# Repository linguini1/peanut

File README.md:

# Peanut 

A modern, tiny, and hackable altimeter for hobby rocketry.

[Peanut is certified as open-source hardware by the Open Source Hardware
Association (CA000081).][oshw-cert]

<p align="center">
    
    <br/>
    Peanut Altimeter with my fingers for scale
</p>

<p align="center">
    
    <br/>
    Peanut Altimeter powered up and operational
</p>

<p align="center">
    
    <br/>
    Peanut Altimeter KiCAD render
</p>

**Features include:**

* Fits in a min-diameter 29mm rocket
* High accuracy barometric pressure sensor (up to ~9km)
* Dual deploy capable (two pyro channels, >1A each)
* Continuity LED indicators for each pyro channel
* Battery reverse polarity protection
* On-board 2MB storage (4MB, 2MB for program, 2MB for logs)
  * Altitude measurements
  * Flight events (ascent, apogee, landing, etc.)
  * Deployment events
* Mach dip filtering (works on flights that break Mach)
* Buzzer arming indicator
* Bluetooth connection
  * Deployment ground testing with flight simulations over BLE
  * Wireless configuration
  * Battery life monitoring
  * Arming verification
  * Continuity & other telemetry over BLE
* WiFi capable

**Tech specs:**

* ESP32C3 MCU (4MB flash, 40KB RAM)
* BMP581 barometer
  * Configured with interrupt line for measurements
  * I2C operated
* Piezo buzzer with GPIO control
* ACAG0201-2450-T 2.4GHz PCB antenna

[Take a look at Peanut's layout and electrical schematics here.][kicad-view]

Peanut is also the subject of one of my [2026 Apache Community over
Code conference presentations][coc-alt-pres]. I discuss the process of designing
an altimeter with NuttX in mind, as well as what considerations go into robust
firmware design.

**Thank you to [PCBWay][pcbway] for sponsoring the manufacture of this project's
PCBs!**

## Firmware

The firmware for this board is made using the [Apache NuttX RTOS][nuttx-site],
an open-source embedded RTOS with an incredible community and an excellent
feature set.

Firmware is spread across a few repositories. If you are compiling yourself,
you'll need:
- [The NuttX kernel source][nuttx]
- [The NuttX application library][nuttx-apps]
- [The Peanut board support package (BSP)][peanut-bsp]
- [My application-level altimeter software,
  `rocket-altimeter`][rocket-altimeter]

Instructions for how to configure, compile and flash firmware can be found in
the [Peanut BSP][peanut-bsp] and [`rocket-altimeter`][rocket-altimeter]
repositories. Pre-built firmware binaries are made available with each release
under the [Peanut BSP][peanut-bsp] repository.

## Hackability

All hardware designs & firmware for Peanut are open-sourced and available under
permissive licensing.

The device itself is programmable over the USB-C interface using Espressif's
`esptool`, so users can tweak the firmware or write their own and easily
re-program the device. Want the buzzer to play custom audio? Want to change the
meaning of the "START" LED? Want to add more features to the Bluetooth
interface, or make the altimeter operate over WiFi instead? You can program
whatever you want into it!

## Physical Integration

If you'd like to fly Peanut, take a look at [the 3D models](./models) so you can
design your av-bay in CAD. This directory also contains the key dimensions of
Peanut for size and mounting holes.

**NOTE:** A user manual for Peanut is coming soon! For now, be aware that Peanut
is only rated for 4V2 LiPo/Li-ion batteries (3V7 nominal). You should only use
batteries _without overcurrent protection_ if you are flying Peanut for
deployment purposes. Otherwise, pyro channels may not be able to draw sufficient
current when fired.

## Make Your Own

If you want to make your own Peanut Altimeter, the component cost for the board
is roughly $35 CAD. You can get PCB blanks from a manufacturer of your choice
(i.e. PCBWay). You should only need to verify the trace widths of the
Bluetooth RF trace depending on the differences between your manufacturer's
PCB stackup and mine.

**NOTE:** This board was not designed with hand-soldering in mind (aside from
the backside). My manufacture process is to use solder paste, a stencil and a
hot plate to do the top-side components. There are 0402 components which are
manageable with steady hands and tweezers.

## On PCBWay

My experience using PCBWay could not have been easier. They provide a plugin for
KiCAD that directly exports your manufacturing files for order to their web
quote interface. I only hand to click the button and choose some parameters for
my board to get everything ordered.

My designs arrived on time, well package and the stencil was really high quality
with a large aluminum frame. I had no issues with the fine details (in copper
and on silkscreen) with such a small board, PCBWay nailed it.

[nuttx]: https://github.com/apache/nuttx
[nuttx-apps]: https://github.com/apache/nuttx-apps
[nuttx-site]: https://nuttx.apache.org/
[rocket-altimeter]: https://github.com/linguini1/rocket-altimeter
[peanut-bsp]: https://github.com/linguini1/peanut-bsp
[pcbway]: https://www.pcbway.com/
[kicad-view]: https://kicanvas.org/?github=https%3A%2F%2Fgithub.com%2Flinguini1%2Fpeanut%2Ftree%2Fmain%2Fpeanut
[coc-alt-pres]: https://web.cvent.com/event/ac71ce47-2b5f-424c-abfe-5b48255315fb/summary?session=b94e377f-e18d-4d64-92bf-246464bb62e4&shareLink=true
[oshw-cert]: https://certification.oshwa.org/ca000081.html

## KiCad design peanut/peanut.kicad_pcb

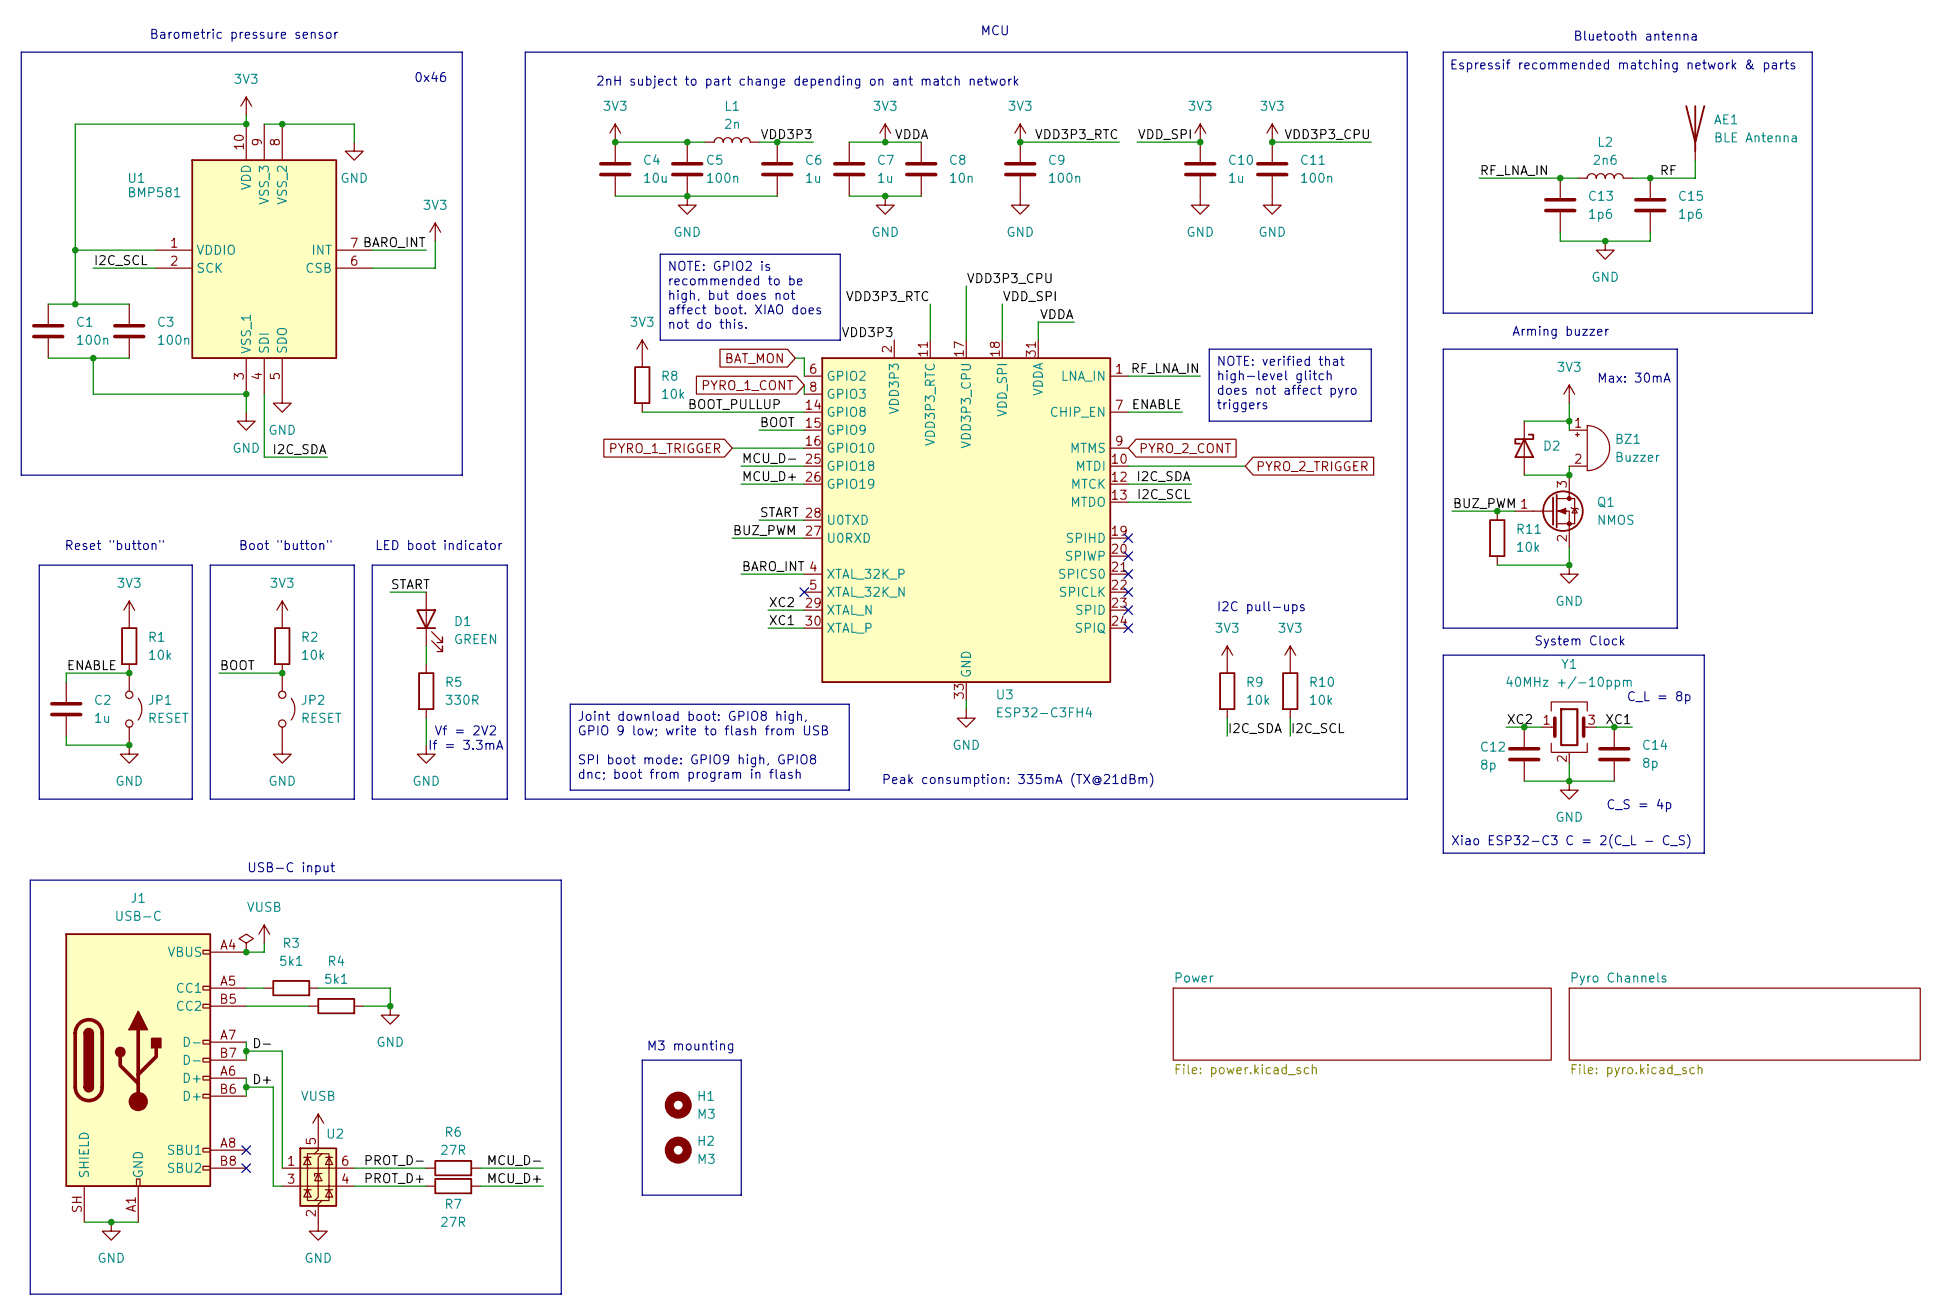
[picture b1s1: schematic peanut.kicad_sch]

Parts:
AE1: BLE Antenna; ANTC2012X70N; MPN ACAG0201-2450-T
BZ1: Buzzer; CMI095503TH; MPN CMI-0955-03TH
C1, C3, C5, C9, C11: 100n; C_0603_1608Metric; MPN KGM15AR70J104KT
C2, C6, C7, C10: 1u; C_0603_1608Metric; MPN 06036C105MAT2A
C4: 10u; C_0603_1608Metric; MPN C1608X5R0J106K080AB
C8: 10n; C_0402_1005Metric; MPN MBASU105SB5103KFNA18
C12, C14: 8p; C_0402_1005Metric; MPN GRM1555C1E8R0DA01D
C13, C15: 1p6; C_0402_1005Metric; MPN RF15N1R6B500CT
D1: GREEN; LED_0805_2012Metric; MPN HSMG-C170
D2: D_SOD-123F; MPN SS25FA
H1, H2: M3; MountingHole_3.2mm_M3_DIN965_Pad_TopOnly
J1: USB-C; USB_C_Receptacle_GCT_USB4105-xx-A_16P_TopMnt_Horizontal; MPN USB4215-03-A
JP1, JP2: RESET; SolderJumper-2_P1.3mm_Open_TrianglePad1.0x1.5mm
L1: 2n; L_0402_1005Metric; MPN 36550402S2N0T
L2: 2n6; C_0402_1005Metric; MPN LQG15WZ2N6B02D
Q1: NMOS; SOT-23-3; MPN BSS123NH6327XTSA1
R1, R2, R8, R9, R10, R11: 10k; R_0402_1005Metric; MPN MCS04020C1002FE000
R3, R4: 5k1; R_0402_1005Metric; MPN MCS04020C5101FE000
R5: 330R; R_0402_1005Metric; MPN 560112110231
R6, R7: 27R; R_0402_1005Metric; MPN ERA-2AKD270X
U1: BMP581; Mouser Part Number 262-BMP581
U2: SOT-23-6; MPN USBLC6-2SC6
U3: ESP32-C3FH4; QFN-32-1EP_5x5mm_P0.5mm_EP3.7x3.7mm; MPN ESP32-C3FH4
Y1: 40MHz +/-10ppm; Crystal_SMD_2016-4Pin_2.0x1.6mm; MPN 830108213209

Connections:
3V3: BZ1.1 (+), C1.1, C3.1, C4.1, C5.1, C7.1, C8.1, C9.1, C10.1, C11.1, D2.1 (K), L1.1, R1.1, R2.1, R8.1, R9.1, R10.1, U1.1 (VDDIO), U1.6 (CSB), U1.10 (VDD), U3.11 (VDD3P3_RTC), U3.17 (VDD3P3_CPU), U3.18 (VDD_SPI), U3.31 (VDDA), U3.32 (VDDA); also elsewhere on the board
/BARO_INT: U1.7 (INT), U3.4 (XTAL_32K_P)
/BOOT: JP2.1 (A), R2.2, U3.15 (GPIO9)
/BOOT_PULLUP: R8.2, U3.14 (GPIO8)
/BUZ_PWM: Q1.1 (G), R11.1, U3.27 (U0RXD)
/D+: J1.A6 (D+), J1.B6 (D+), U2.3 (I/O2)
/D-: J1.A7 (D-), J1.B7 (D-), U2.1 (I/O1)
/ENABLE: C2.1, JP1.1 (A), R1.2, U3.7 (CHIP_EN)
/I2C_SCL: R10.2, U1.2 (SCK), U3.13 (MTDO)
/I2C_SDA: R9.2, U1.4 (SDI), U3.12 (MTCK)
/MCU_D+: R7.2, U3.26 (GPIO19)
/MCU_D-: R6.2, U3.25 (GPIO18)
/PROT_D+: R7.1, U2.4 (I/O2)
/PROT_D-: R6.1, U2.6 (I/O1)
/RF: AE1.1 (A_1), C15.1, L2.2
/RF_LNA_IN: C13.1, L2.1, U3.1 (LNA_IN)
/START: D1.2 (A), U3.28 (U0TXD)
/VDD3P3: C6.1, L1.2, U3.2 (VDD3P3), U3.3 (VDD3P3)
/XC1: C14.1, U3.30 (XTAL_P), Y1.3
/XC2: C12.1, U3.29 (XTAL_N), Y1.1
BAT_MON: U3.6 (GPIO2); also elsewhere on the board
GND: C1.2, C2.2, C3.2, C4.2, C5.2, C6.2, C7.2, C8.2, C9.2, C10.2, C11.2, C12.2, C13.2, C14.2, C15.2, J1.A1 (GND), J1.A12 (GND), J1.B1 (GND), J1.B12 (GND), J1.SH (SHIELD), JP1.2 (B), JP2.2 (B), Q1.2 (S), R3.2, R4.2, R5.2, R11.2, U1.3 (VSS_1), U1.5 (SDO), U1.8 (VSS_2), U1.9 (VSS_3), U2.2 (GND), U3.33 (GND), Y1.2 (G), Y1.4 (G); also elsewhere on the board
unnamed: BZ1.2 (-), D2.2 (A), Q1.3 (D)
unnamed: D1.1 (K), R5.1
unnamed: J1.A5 (CC1), R3.1
unnamed: J1.B5 (CC2), R4.1
PYRO_1_CONT: U3.8 (GPIO3); also elsewhere on the board
PYRO_1_TRIGGER: U3.16 (GPIO10); also elsewhere on the board
PYRO_2_CONT: U3.9 (MTMS); also elsewhere on the board
PYRO_2_TRIGGER: U3.10 (MTDI); also elsewhere on the board
VUSB: J1.A4 (VBUS), J1.A9 (VBUS), J1.B4 (VBUS), J1.B9 (VBUS), U2.5 (VBUS); also elsewhere on the board

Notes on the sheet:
USB-C input
M3 mounting
Bluetooth antenna
Reset "button"
Espressif recommended matching network & parts
Peak consumption: 335mA (TX@21dBm)
I2C pull-ups
System Clock
Max: 30mA
Xiao ESP32-C3
Arming buzzer
2nH subject to part change depending on ant match network
LED boot indicator
0x46
Boot "button"
C = 2(C_L - C_S)
C_S = 4p
Barometric pressure sensor
Vf = 2V2 If = 3.3mA
MCU
C_L = 8p
Joint download boot: GPIO8 high, GPIO 9 low; write to flash from USB SPI boot mode: GPIO9 high, GPIO8 dnc; boot from program in flash
NOTE: verified that high-level glitch does not affect pyro triggers
NOTE: GPIO2 is recommended to be high, but does not affect boot. XIAO does not do this.

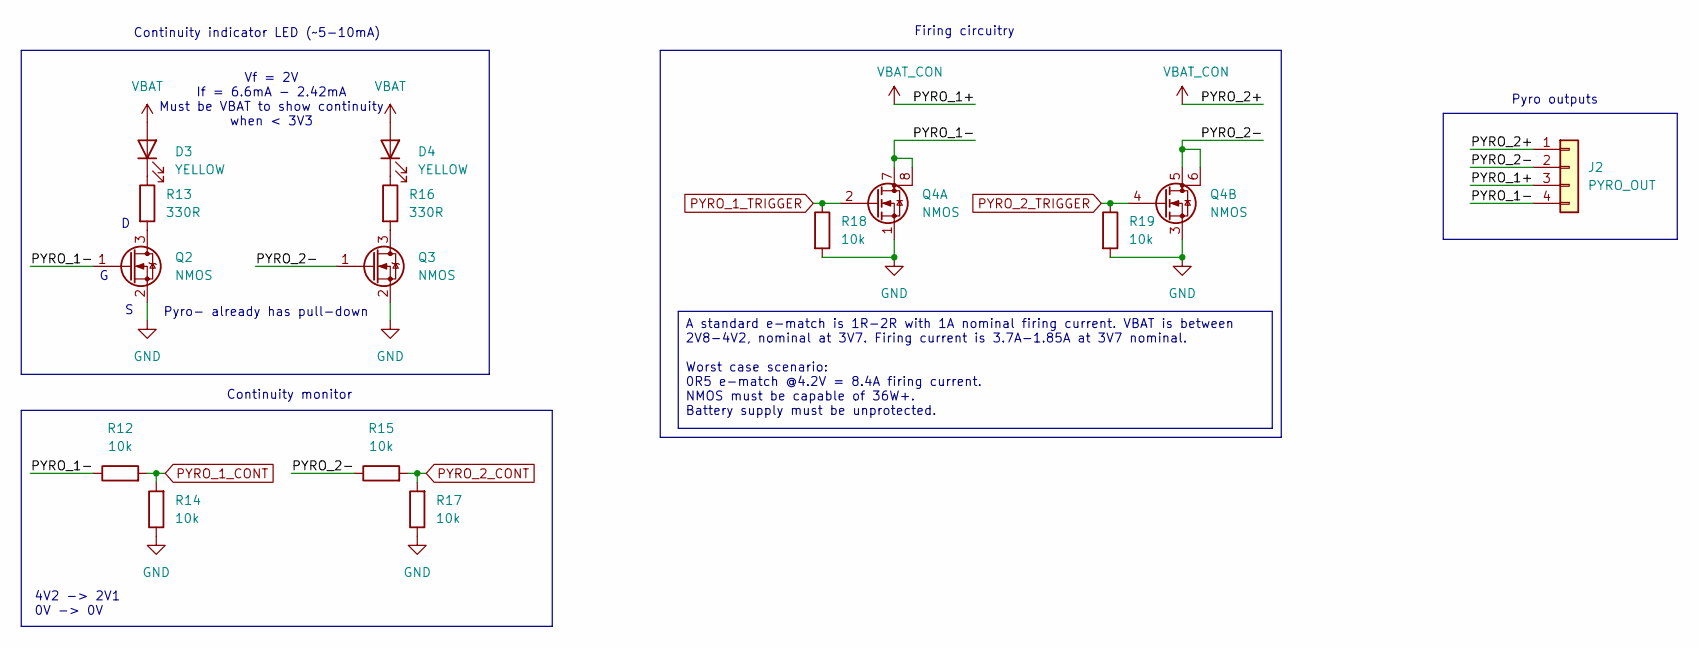
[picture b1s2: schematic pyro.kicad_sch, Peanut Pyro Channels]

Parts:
D3, D4: YELLOW; LED_0805_2012Metric; MPN 599-1140-147F
J2: PYRO_OUT; TerminalBlock_Phoenix_MKDS-1-4-3.81_1x04_P3.81mm_Horizontal; MPN 1727036
Q2, Q3: NMOS; SOT-23-3; MPN BSS123NH6327XTSA1
Q4: NMOS; TSM200N03DPQ33RGG; MPN TSM200N03DPQ33 RGG
R12, R14, R15, R17, R18, R19: 10k; R_0402_1005Metric; MPN MCS04020C1002FE000
R13, R16: 330R; R_0402_1005Metric; MPN 560112110231

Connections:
/Pyro Channels/PYRO_1-: J2.4, Q2.1 (G), Q4.7 (D), Q4.8 (D), Q4.10, R12.1
/Pyro Channels/PYRO_2-: J2.2, Q3.1 (G), Q4.5 (D), Q4.6 (D), Q4.9, R15.1
GND: Q2.2 (S), Q3.2 (S), Q4.1 (S), Q4.3 (S), R14.1, R17.1, R18.2, R19.2; also elsewhere on the board
unnamed: D3.1 (K), R13.1
unnamed: D4.1 (K), R16.1
unnamed: Q2.3 (D), R13.2
unnamed: Q3.3 (D), R16.2
PYRO_1_CONT: R12.2, R14.2; also elsewhere on the board
PYRO_1_TRIGGER: Q4.2 (G), R18.1; also elsewhere on the board
PYRO_2_CONT: R15.2, R17.2; also elsewhere on the board
PYRO_2_TRIGGER: Q4.4 (G), R19.1; also elsewhere on the board
VBAT: D3.2 (A), D4.2 (A); also elsewhere on the board
VBAT_CON: J2.1, J2.3; also elsewhere on the board

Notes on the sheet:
Firing circuitry
Pyro outputs
Vf = 2V If = 6.6mA - 2.42mA Must be VBAT to show continuity when < 3V3
4V2 -> 2V1 0V -> 0V
Continuity indicator LED (~5-10mA)
Pyro- already has pull-down
Continuity monitor
A standard e-match is 1R-2R with 1A nominal firing current. VBAT is between 2V8-4V2, nominal at 3V7. Firing current is 3.7A-1.85A at 3V7 nominal. Worst case scenario: 0R5 e-match @4.2V = 8.4A firing current. NMOS must be capable of 36W+. Battery supply must be unprotected.

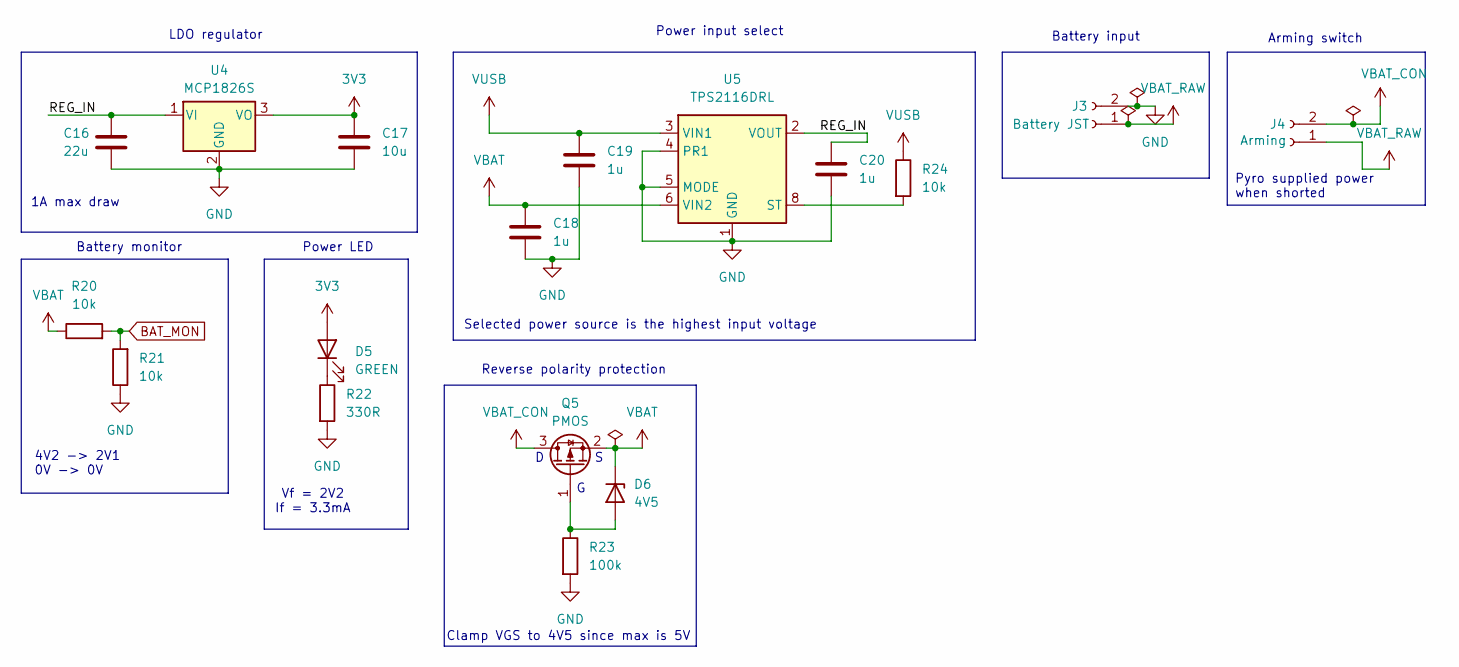
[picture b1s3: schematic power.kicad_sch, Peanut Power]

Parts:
C16: 22u; C_0603_1608Metric; MPN MLASJ168BB5226MTNA01
C17: 10u; C_0603_1608Metric; MPN C1608X5R0J106K080AB
C18, C19, C20: 1u; C_0603_1608Metric; MPN 06036C105MAT2A
D5: GREEN; LED_0805_2012Metric; MPN HSMG-C170
D6: 4V5; D_SOD-323_HandSoldering; MPN PDZ4.3BZ
J3: Battery JST; JST_PH_S2B-PH-K_1x02_P2.00mm_Horizontal; MPN S2B-PH-K-S(LF)(SN)(PP)
J4: Arming; TerminalBlock_Phoenix_MPT-0,5-2-2.54_1x02_P2.54mm_Horizontal; MPN 1725656
Q5: PMOS; SOT-23; MPN SI2329DS-T1-GE3
R20, R21, R24: 10k; R_0402_1005Metric; MPN MCS04020C1002FE000
R22: 330R; R_0402_1005Metric; MPN 560112110231
R23: 100k; R_0603_1608Metric; MPN ERA-3AED104V
U4: MCP1826S; SOT-223-3_TabPin2; MPN MCP1826S-3302E/DB
U5: TPS2116DRL; SOT-583-8; MPN TPS2116DRLR

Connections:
3V3: C17.1, D5.2 (A), U4.3 (VO); also elsewhere on the board
/Power/REG_IN: C16.1, C20.1, U4.1 (VI), U5.2 (VOUT), U5.7 (VOUT)
BAT_MON: R20.2, R21.2; also elsewhere on the board
GND: C16.2, C17.2, C18.2, C19.2, C20.2, J3.2, R21.1, R22.2, R23.2, U4.2 (GND), U5.1 (GND), U5.4 (PR1), U5.5 (MODE); also elsewhere on the board
unnamed: D5.1 (K), R22.1
unnamed: D6.2 (A), Q5.1 (G), R23.1
unnamed: R24.2, U5.8 (ST)
VBAT: C18.1, D6.1 (K), Q5.2 (S), R20.1, U5.6 (VIN2); also elsewhere on the board
VBAT_CON: J4.2, Q5.3 (D); also elsewhere on the board
VBAT_RAW: J3.1, J4.1
VUSB: C19.1, R24.1, U5.3 (VIN1); also elsewhere on the board

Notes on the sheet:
4V2 -> 2V1 0V -> 0V
LDO regulator
Vf = 2V2 If = 3.3mA
Clamp VGS to 4V5 since max is 5V
Reverse polarity protection
1A max draw
Battery monitor
Power input select
Arming switch
Battery input
Power LED
Selected power source is the highest input voltage
Pyro supplied power when shorted

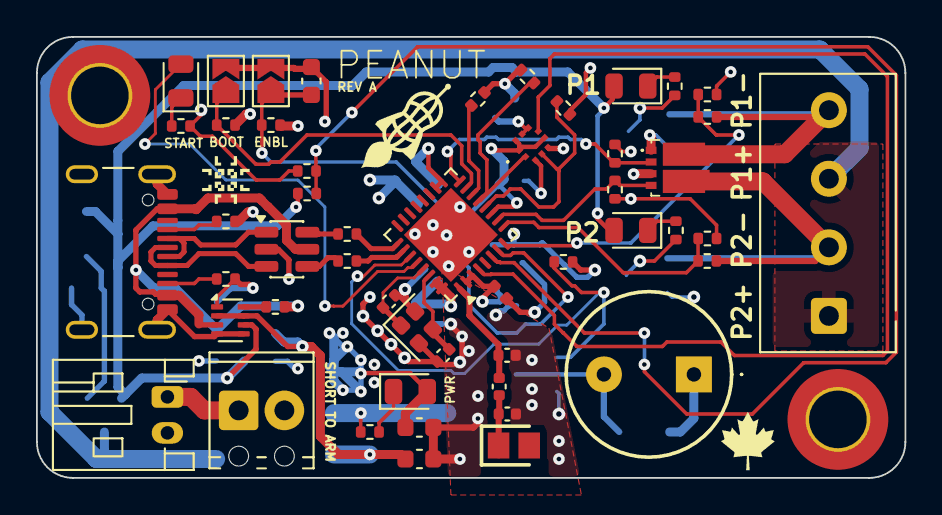
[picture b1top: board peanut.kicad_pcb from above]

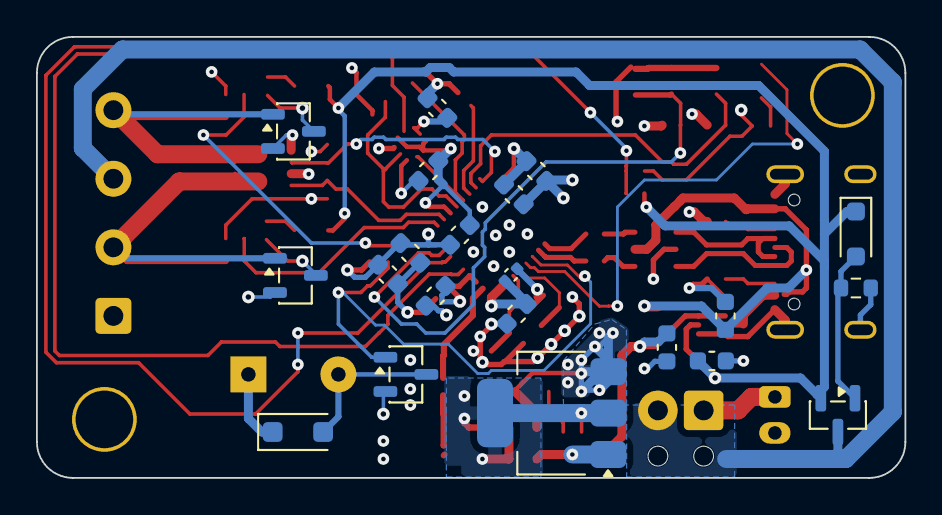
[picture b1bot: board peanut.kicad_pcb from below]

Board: 4 copper layers, 48.2 x 24.5 mm, 73 parts (21 on the bottom side), 44 nets.

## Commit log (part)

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2026-01-03 Initial commit.
2026-01-06 More tweaks
2026-02-24 Assigned some actual parts and footprints to symbols.
2026-02-25 Footprint assignments for dual-channel NMOS; picked some more parts
2026-02-25 More component MPNs
2026-04-27 feat: Finish schematic
    This commit "completes" the schematic to the best of my foresight for
    the moment. All components have BOM MPNs and footprints assigned. I have
    double checked pins on the 40MHz clock and that pin assignments on the
    MCU are valid. I have selected a chip antenna with high gain, added
    decoupling capacitors to the MCU, picked out terminal blocks and
    followed the Espressif schematic guide. A preliminary layout can be
2026-04-28 feat: Initial layout
    I have roughed out the initial PCB layout. It is wider than I'd like,
    and not near a peanut shape. It appears the "start" and "panic" LEDs
    never had pins assigned to them. I think I will replace the MCU RX & TX
    with these instead, since I can still use the RX and TX as probe pads
    that way.
2026-04-28 bug: Fix missing connections to START/PANIC LEDs
    The START/PANIC LEDs now take over the UART interface. If UART is
    needed, using the pads of the LEDS should not be functionally different
    than using the test points.
2026-04-28 feat: Remove secondary crystal oscillator
    We will rely on the internal crystal oscillator: it is cheaper, saves me
    headaches routing the RF stuff and removes an unnecessary component.
2026-04-28 bug: Buzzer not connected
    Fixed the buzzer line not being connected to anything by replacing the
    PANIC LED with it. Buzzing during panic is equally acceptable, if not
    annoying, while debugging.
2026-04-29 feat: Mounting holes
    Added M3 mounting holes.
2026-04-29 feat: Better layout
2026-04-29 feat: Added necessary silkscreen information
2026-04-29 feat: Added inner layer pours
2026-04-29 feat: Add review checklist
    Preliminary review checklist to make sure that everything is correct
    before ordering/finalizing the design.
2026-04-29 feat: 100n capacitors to 0603
    Since there is sufficient space, the 100n capacitors have been increased
    to 0603 size and all placed on the back of the board. This allows the
    board to be squished in further slightly.
2026-04-29 feat: Shrink board
    Shrinks the board length-wise more.
2026-04-29 feat: Verify component features
    Completed most of the review checklist for the initial revision. Routing
    can commence once design rules are updated.
2026-04-30 feat: Cheaper inductor
    Swapped inductor for one that is cheaper. Current board cost (minus JST
    connector since that is not available on Mouser) is $44.76 CAD in
    components.
2026-04-30 feat: Solder jumpers instead of capacitor footprint
    The boot and enable jumpers are now solder jumpers instead of capacitors
    footprints, which should make them easier to jump.
2026-04-30 feat: Add silkscreen logo
    Adds a board logo and my logo to the board silkscreen.
2026-04-30 feat: Initial routing
    Initial, rough routing of traces.
2026-04-30 feat: Add image to README
    README file now has something interesting to look at and some better
    information about the project.
2026-04-30 chore: Fix all DRC issues except RF routing
2026-04-30 chore: Specify range of barometer
2026-04-30 feat: Open Source Hardware silkscreen
2026-05-01 chore: Mention min-diameter 29mm form-factor
2026-05-01 feat: Route the Bluetooth trace
2026-05-01 bug: Fix arming flaw
    Fixed the arming circuitry so that the ARM terminal prevents power going
    to the pyro channels. This means that the rest of the board can be
    powered on before arming, which is good because:
    - It allows configuring without arming
    - Software arming can still be done as a second stage
    - The MCU can be in low-power mode until told to arm over BLE
2026-05-01 chore: Clean up routing
    Cleaned up some traces and added teardrops.
2026-05-01 chore: ignore gerbers
2026-05-01 chore: More MCU ground vias
2026-05-01 chore: add dimensions
2026-05-01 chore: update render
2026-05-01 chore: fix inductor footprint size
2026-05-05 feat: Better arming circuit
    Improved the arming circuit connections so that both circuits are
    powered off until armed.
2026-05-07 feat: Move USB closer to the edge.
2026-05-28 chore: add CHIP_EN capacitor
2026-05-28 chore: add flyback diode to buzzer
2026-05-28 chore: updated RF components to 0402
2026-05-28 chore: remove mention of 0201 components
2026-05-28 chore: replace switching regulator with LDO
2026-05-28 chore: fix bulk capacitance value based on easymini selected value
2026-05-28 feat: move to TAPR open hardware license
2026-05-28 Fix ADC voltage monitoring to use 1:1 ratio
2026-05-29 feat: improve reverse polarity protection circuit
2026-05-29 feat: change LDO again to something with better dropout voltage
2026-05-29 chore: re-annotate
2026-05-29 feat: changed pressure sensor to BMP581
2026-05-29 feat: new routing done
2026-05-29 feat: Added copper keepout for antenna
    NOTE: did not follow the recommended layout exactly, so this is adapted
    as best as possible.
2026-05-29 chore: resolve DRC errors
2026-05-29 chore: remove todos
2026-05-29 chore: new render
2026-05-29 chore: new BOM
2026-05-29 chore: remove review checklist due to significant modifications
2026-05-29 chore: update README to reflect changes
2026-05-29 chore: save project file
2026-06-02 feat: add the maple leaf
2026-06-02 feat: finished review; swapped battery lead polarity to match other rocket electronics
2026-06-17 chore: provide link to BSP
2026-06-17 chore: update docs to reflect storage sizes
